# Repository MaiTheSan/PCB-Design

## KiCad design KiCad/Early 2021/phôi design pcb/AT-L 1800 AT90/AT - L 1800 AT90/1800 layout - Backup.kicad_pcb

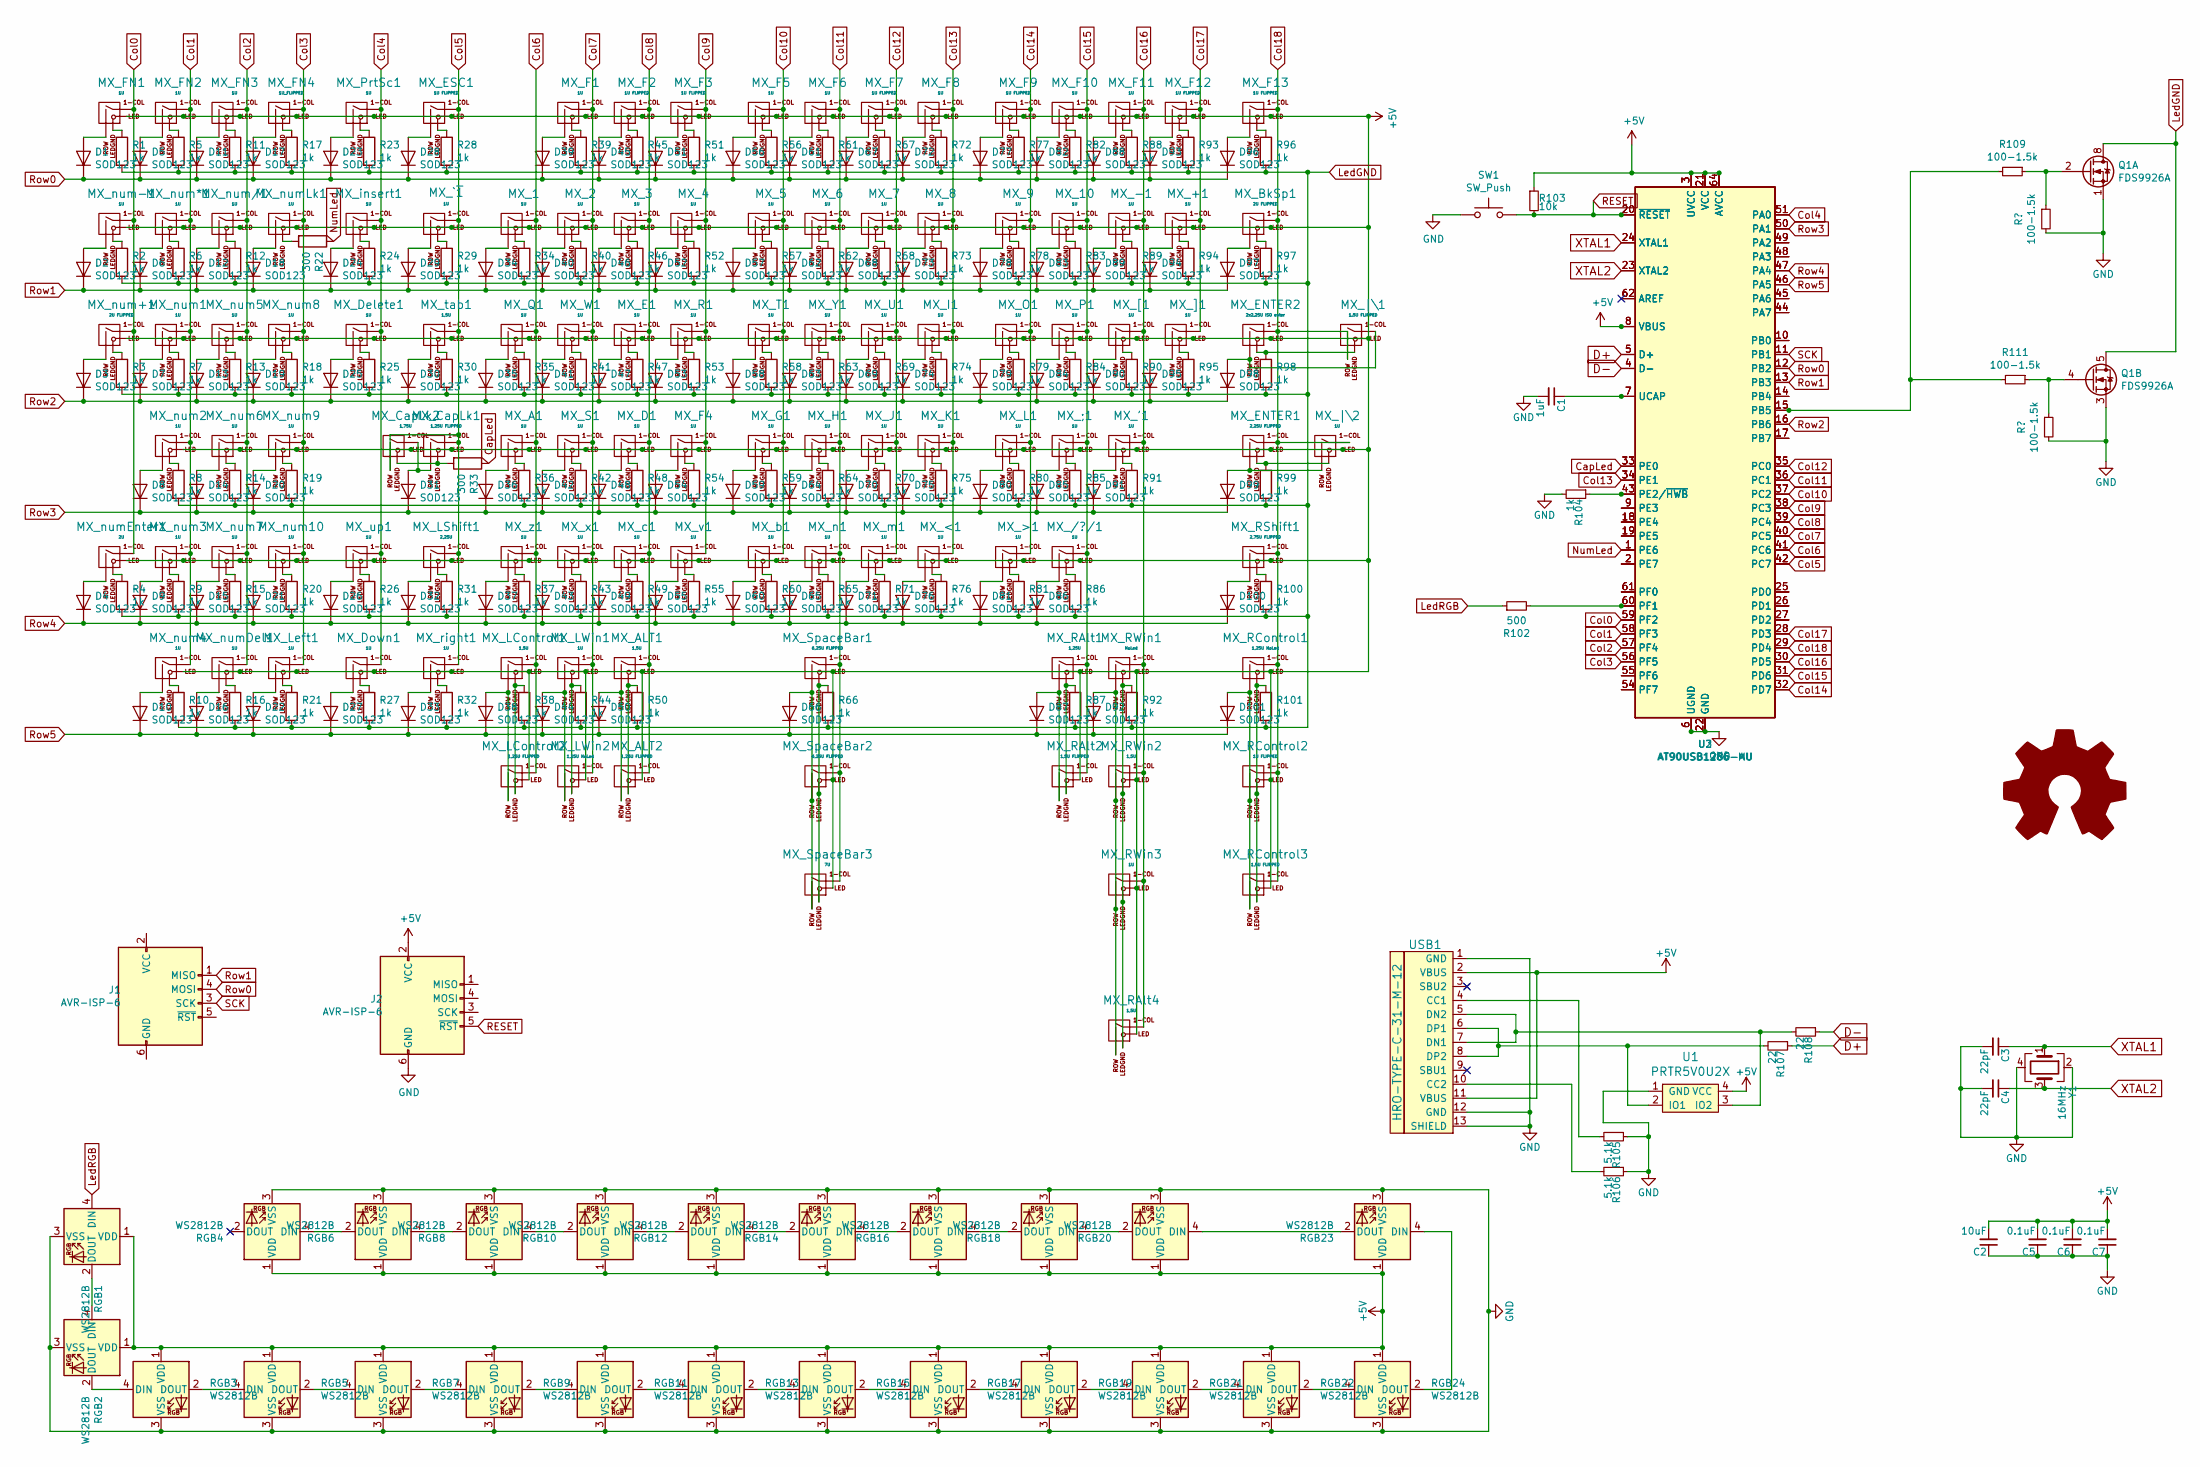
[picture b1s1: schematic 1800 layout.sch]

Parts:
C1: 1uF; C_0603
C2: 10uF; C_0603
C3, C4: 22pF; C_0603
C5, C6, C7: 0.1uF; C_0603
D1, D2, D3, D4, D5, D6, D7, D8, D9, D10, D11, D12, D13, D14, D15, D16, D17, D18, D19, D20, D21, D22, D23, D24, D25, D26, D27, D28, D29, D30, D31, D32, D33, D34, D35, D36, D37, D38, D39, D40, D41, D42, D43, D44, D45, D46, D47, D48, D49, D50, D51, D52, D53, D54, D55, D56, D57, D58, D59, D60, D61, D62, D63, D64, D65, D66, D67, D68, D69, D70, D71, D72, D73, D74, D75, D76, D77, D78, D79, D80, D81, D82, D83, D84, D85, D86, D87, D88, D89, D90, D91, D92, D93, D94, D95, D96, D97, D98, D99, D101: SOD123; D_SOD-123
D100: SOD123; D_SOD-123-Pretty
J1, J2: AVR-ISP-6; Reset_Pretty
LOGO1: Logo_Open_Hardware_Large; sanpjxlogo
MX_1, MX_2, MX_3, MX_4, MX_5, MX_6, MX_7, MX_8, MX_9, MX_10: 1U; MXOnly-1U
MX_'1: 1U; MXOnly-1U
MX_+1: 1U; MXOnly-1U
MX_-1: 1U; MXOnly-1U
MX_/?/1: 1U; MXOnly-1U
MX_;1: 1U; MXOnly-1U
MX_<1: 1U; MXOnly-1U
MX_>1: 1U; MXOnly-1U
MX_A1: 1U; MXOnly-1U
MX_ALT1: 1,5U; MXOnly-1.5U
MX_ALT2: 1,25U FLIPPED; MXOnly-1.25U-FLIPPED
MX_BkSp1: 2U FLIPPED; MXOnly-2U-FLIPPED
MX_CapLk1: 1,25U FLIPPED; MXOnly-1.25U-FLIPPED
MX_CapLk2: 1,75U; MXOnly-1.75U
MX_D1: 1U; MXOnly-1U
MX_Delete1: 1U; MXOnly-1U
MX_Down1: 1U; MXOnly-1U-FLIPPED
MX_E1: 1U; MXOnly-1U
MX_ENTER1: 2,25U FLIPPED; MXOnly-2.25U-FLIPPED-ReversedStabilizers
MX_ENTER2: 2x2.25U ISO enter; MXOnly-ISO
MX_ESC1: 1U FLIPPED; MXOnly-1U-FLIPPED
MX_F1, MX_F4, MX_F6, MX_F8, MX_F10, MX_F11: 1U; MXOnly-1U
MX_F2, MX_F3, MX_F7, MX_F9, MX_F12, MX_F13: 1U FLIPPED; MXOnly-1U-FLIPPED
MX_F5: 1U; MXOnly-1U-FLIPPED
MX_FN1, MX_FN2, MX_FN3: 1U; MXOnly-1U
MX_FN4: 1U_FLIPPED; MXOnly-1U-FLIPPED
MX_G1: 1U; MXOnly-1U
MX_H1: 1U; MXOnly-1U
MX_I1: 1U; MXOnly-1U
MX_J1: 1U; MXOnly-1U
MX_K1: 1U; MXOnly-1U
MX_L1: 1U; MXOnly-1U
MX_LControl1: 1,5U; MXOnly-1.5U
MX_LControl2: 1,25U FLIPPED; MXOnly-1.25U-FLIPPED
MX_LShift1: 2,25U; MXOnly-2.25U
MX_LWin1: 1U; MXOnly-1U
MX_LWin2: 1,25U NoLed; MXOnly-1.25U-FLIPPED
MX_Left1: 1U; MXOnly-1U
MX_O1: 1U; MXOnly-1U
MX_P1: 1U; MXOnly-1U
MX_PrtSc1: 1U; MXOnly-1U
MX_Q1: 1U; MXOnly-1U
MX_R1: 1U; MXOnly-1U
MX_RAlt1: 1,25U; MXOnly-1.25U
MX_RAlt2: 1,5U FLIPPED; MXOnly-1.5U-FLIPPED
MX_RAlt4: 1,5U; MXOnly-1.5U
MX_RControl1: 1,25U NoLed; MXOnly-1.25U
MX_RControl2: 1U FLIPPED; MXOnly-1U-FLIPPED
MX_RControl3: 1,5U FLIPPED; MXOnly-1.5U-FLIPPED
MX_RShift1: 2,75U FLIPPED; MXOnly-2.75U-FLIPPED
MX_RWin1: NoLed; MXOnly-1.25U-FLIPPED
MX_RWin2: 1,5U; MXOnly-1.5U
MX_RWin3: 1U; MXOnly-1U
MX_S1: 1U; MXOnly-1U
MX_SpaceBar1, MX_SpaceBar2: 6,25U FLIPPED; MXOnly-6.25U-FLIPPED-ReversedStabilizers
MX_SpaceBar3: 7U; MXOnly-7U-ReversedStabilizers
MX_T1: 1U; MXOnly-1U
MX_U1: 1U; MXOnly-1U
MX_W1: 1U; MXOnly-1U
MX_Y1: 1U; MXOnly-1U
MX_[1: 1U; MXOnly-1U
MX_]1: 1U; MXOnly-1U
MX_`~1: 1U; MXOnly-1U
MX_b1: 1U; MXOnly-1U
MX_c1: 1U; MXOnly-1U
MX_insert1: 1U; MXOnly-1U
MX_m1: 1U; MXOnly-1U
MX_n1: 1U; MXOnly-1U
MX_num1, MX_num2, MX_num3, MX_num4, MX_num5, MX_num6, MX_num7, MX_num9, MX_num10: 1U; MXOnly-1U
MX_num8: 1U; MXOnly-1U-FLIPPED
MX_num*1: 1U; MXOnly-1U
MX_num+1: 2U FLIPPED; MXOnly-2U
MX_num-1: 1U; MXOnly-1U
MX_num/1: 1U; MXOnly-1U
MX_numDel1: 1U; MXOnly-1U
MX_numEnter1: 2U; MXOnly-2U
MX_numLk1: 1U; MXOnly-1U
MX_right1: 1U; MXOnly-1U
MX_tab1: 1,5U; MXOnly-1.5U
MX_up1: 1U; MXOnly-1U
MX_v1: 1U; MXOnly-1U
MX_x1: 1U; MXOnly-1U
MX_z1: 1U; MXOnly-1U
MX_|\1: 1.5U FLIPPED; MXOnly-1.5U-FLIPPED
MX_|\2: 1U; MXOnly-1U
Q1: FDS9926A; SOIC-8_3.9x4.9mm_P1.27mm
R1, R2, R3, R4, R5, R6, R7, R8, R9, R10, R11, R12, R13, R14, R15, R16, R17, R18, R19, R20, R21, R23, R24, R25, R26, R27, R28, R29, R30, R31, R32, R34, R35, R36, R37, R38, R39, R40, R41, R42, R43, R44, R45, R46, R47, R48, R49, R50, R51, R52, R53, R54, R55, R56, R57, R58, R59, R60, R61, R62, R63, R64, R65, R66, R67, R68, R69, R70, R71, R72, R73, R74, R75, R76, R77, R78, R79, R80, R81, R82, R83, R84, R85, R86, R87, R88, R89, R90, R91, R92, R93, R94, R95, R96, R97, R98, R99, R100, R101, R104: 1k; R_0805
R22, R33: 300; R_0805
R102: 500; R_0805
R103: 10k; R_0805
R105, R106: 5.1k; C_0603
R107, R108: 22; C_0603
R109, R111: 100-1.5k; R_0805
RGB1, RGB2, RGB3, RGB4, RGB5, RGB6, RGB7, RGB8, RGB9, RGB10, RGB11, RGB12, RGB13, RGB14, RGB15, RGB16, RGB17, RGB18, RGB19, RGB20, RGB21, RGB22, RGB23, RGB24: WS2812B; LED_WS2812B_PLCC4_5.0x5.0mm_P3.2mm
SW1: SW_Push; SKQG-1155865
U1: PRTR5V0U2X; SOT143B
U2: AT90USB1286-AU; TQFP-64_14x14mm_P0.8mm
U3: AT90USB1286-MU; QFN-64-1EP_9x9mm_P0.5mm_EP7.5x7.5mm
USB1: HRO-TYPE-C-31-M-12; HRO-TYPE-C-31-M-12-Assembly
Y1: 16MHz; Crystal_SMD_3225-4Pin_3.2x2.5mm

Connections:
+5V: C2.2, C5.2, C6.2, C7.2, J2.2 (VCC), MX_1.3 (LED), MX_2.3 (LED), MX_3.3 (LED), MX_4.3 (LED), MX_5.3 (LED), MX_6.3 (LED), MX_7.3 (LED), MX_8.3 (LED), MX_9.3 (LED), MX_10.3 (LED), MX_'1.3 (LED), MX_+1.3 (LED), MX_-1.3 (LED), MX_/?/1.3 (LED), MX_;1.3 (LED), MX_<1.3 (LED), MX_>1.3 (LED), MX_A1.3 (LED), MX_ALT1.3 (LED), MX_ALT2.3 (LED), MX_BkSp1.3 (LED), MX_CapLk1.3 (LED), MX_CapLk2.3 (LED), MX_D1.3 (LED), MX_Delete1.3 (LED), MX_Down1.3 (LED), MX_E1.3 (LED), MX_ENTER1.3 (LED), MX_ENTER2.3 (LED), MX_ESC1.3 (LED), MX_F1.3 (LED), MX_F2.3 (LED), MX_F3.3 (LED), MX_F4.3 (LED), MX_F5.3 (LED), MX_F6.3 (LED), MX_F7.3 (LED), MX_F8.3 (LED), MX_F9.3 (LED), MX_F10.3 (LED), MX_F11.3 (LED), MX_F12.3 (LED), MX_F13.3 (LED), MX_FN1.3 (LED), MX_FN2.3 (LED), MX_FN3.3 (LED), MX_FN4.3 (LED), MX_G1.3 (LED), MX_H1.3 (LED), MX_I1.3 (LED), MX_J1.3 (LED), MX_K1.3 (LED), MX_L1.3 (LED), MX_LControl1.3 (LED), MX_LControl2.3 (LED), MX_LShift1.3 (LED), MX_LWin1.3 (LED), MX_LWin2.3 (LED), MX_Left1.3 (LED), MX_O1.3 (LED), MX_P1.3 (LED), MX_PrtSc1.3 (LED), MX_Q1.3 (LED), MX_R1.3 (LED), MX_RAlt1.3 (LED), MX_RAlt2.3 (LED), MX_RAlt4.3 (LED), MX_RControl1.3 (LED), MX_RControl2.3 (LED), MX_RControl3.3 (LED), MX_RShift1.3 (LED), MX_RWin1.3 (LED), MX_RWin2.3 (LED), MX_RWin3.3 (LED), MX_S1.3 (LED), MX_SpaceBar1.3 (LED), MX_SpaceBar2.3 (LED), MX_SpaceBar3.3 (LED), MX_T1.3 (LED), MX_U1.3 (LED), MX_W1.3 (LED), MX_Y1.3 (LED), MX_[1.3 (LED), MX_]1.3 (LED), MX_`~1.3 (LED), MX_b1.3 (LED), MX_c1.3 (LED), MX_insert1.3 (LED), MX_m1.3 (LED), MX_n1.3 (LED), MX_num1.3 (LED), MX_num2.3 (LED), MX_num3.3 (LED), MX_num4.3 (LED), MX_num5.3 (LED), MX_num6.3 (LED), MX_num7.3 (LED), MX_num8.3 (LED), MX_num9.3 (LED), MX_num10.3 (LED), MX_num*1.3 (LED), MX_num+1.3 (LED), MX_num-1.3 (LED), MX_num/1.3 (LED), MX_numDel1.3 (LED), MX_numEnter1.3 (LED), MX_numLk1.3 (LED), MX_right1.3 (LED), MX_tab1.3 (LED), MX_up1.3 (LED), MX_v1.3 (LED), MX_x1.3 (LED), MX_z1.3 (LED), MX_|\1.3 (LED), MX_|\2.3 (LED), R103.1, RGB1.1 (VDD), RGB2.1 (VDD), RGB3.1 (VDD), RGB4.1 (VDD), RGB5.1 (VDD), RGB6.1 (VDD), RGB7.1 (VDD), RGB8.1 (VDD), RGB9.1 (VDD), RGB10.1 (VDD), RGB11.1 (VDD), RGB12.1 (VDD), RGB13.1 (VDD), RGB14.1 (VDD), RGB15.1 (VDD), RGB16.1 (VDD), RGB17.1 (VDD), RGB18.1 (VDD), RGB19.1 (VDD), RGB20.1 (VDD), RGB21.1 (VDD), RGB22.1 (VDD), RGB23.1 (VDD), RGB24.1 (VDD), U1.4 (VCC), U2.3 (UVCC), U2.8 (VBUS), U2.21 (VCC), U2.52 (VCC), U2.64 (AVCC), U3.3 (UVCC), U3.8 (VBUS), U3.21 (VCC), U3.52 (VCC), U3.64 (AVCC), USB1.2 (VBUS), USB1.11 (VBUS)
CapLed: R33.1, U2.33 (PE0), U3.33 (PE0)
Col0: MX_FN1.1 (COL), MX_num+1.1 (COL), MX_num-1.1 (COL), MX_numEnter1.1 (COL), U2.59 (PF2), U3.59 (PF2)
Col1: MX_FN2.1 (COL), MX_num1.1 (COL), MX_num2.1 (COL), MX_num3.1 (COL), MX_num4.1 (COL), MX_num*1.1 (COL), U2.58 (PF3), U3.58 (PF3)
Col2: MX_FN3.1 (COL), MX_num5.1 (COL), MX_num6.1 (COL), MX_num7.1 (COL), MX_num/1.1 (COL), MX_numDel1.1 (COL), U2.57 (PF4), U3.57 (PF4)
Col3: MX_FN4.1 (COL), MX_Left1.1 (COL), MX_num8.1 (COL), MX_num9.1 (COL), MX_num10.1 (COL), MX_numLk1.1 (COL), U2.56 (PF5), U3.56 (PF5)
Col4: MX_Delete1.1 (COL), MX_Down1.1 (COL), MX_PrtSc1.1 (COL), MX_insert1.1 (COL), MX_up1.1 (COL), U2.51 (PA0), U3.51 (PA0)
Col5: MX_CapLk1.1 (COL), MX_CapLk2.2 (ROW), MX_ESC1.1 (COL), MX_LShift1.1 (COL), MX_`~1.1 (COL), MX_right1.1 (COL), MX_tab1.1 (COL), U2.42 (PC7), U3.42 (PC7)
Col6: MX_1.1 (COL), MX_A1.1 (COL), MX_LControl1.1 (COL), MX_LControl2.1 (COL), MX_Q1.1 (COL), MX_z1.1 (COL), U2.41 (PC6), U3.41 (PC6)
Col7: MX_2.1 (COL), MX_F1.1 (COL), MX_LWin1.1 (COL), MX_LWin2.1 (COL), MX_S1.1 (COL), MX_W1.1 (COL), MX_x1.1 (COL), U2.40 (PC5), U3.40 (PC5)
Col8: MX_3.1 (COL), MX_ALT1.1 (COL), MX_ALT2.1 (COL), MX_D1.1 (COL), MX_E1.1 (COL), MX_F2.1 (COL), MX_c1.1 (COL), U2.39 (PC4), U3.39 (PC4)
Col9: MX_4.1 (COL), MX_F3.1 (COL), MX_F4.1 (COL), MX_R1.1 (COL), MX_v1.1 (COL), U2.38 (PC3), U3.38 (PC3)
Col10: MX_5.1 (COL), MX_F5.1 (COL), MX_G1.1 (COL), MX_T1.1 (COL), MX_b1.1 (COL), U2.37 (PC2), U3.37 (PC2)
Col11: MX_6.1 (COL), MX_F6.1 (COL), MX_H1.1 (COL), MX_SpaceBar1.1 (COL), MX_SpaceBar2.1 (COL), MX_SpaceBar3.1 (COL), MX_Y1.1 (COL), MX_n1.1 (COL), U2.36 (PC1), U3.36 (PC1)
Col12: MX_7.1 (COL), MX_F7.1 (COL), MX_J1.1 (COL), MX_U1.1 (COL), MX_m1.1 (COL), U2.35 (PC0), U3.35 (PC0)
Col13: MX_8.1 (COL), MX_<1.1 (COL), MX_F8.1 (COL), MX_I1.1 (COL), MX_K1.1 (COL), U2.34 (PE1), U3.34 (PE1)
Col14: MX_9.1 (COL), MX_>1.1 (COL), MX_F9.1 (COL), MX_L1.1 (COL), MX_O1.1 (COL), U2.32 (PD7), U3.32 (PD7)
Col15: MX_10.1 (COL), MX_/?/1.1 (COL), MX_;1.1 (COL), MX_F10.1 (COL), MX_P1.1 (COL), MX_RAlt1.1 (COL), MX_RAlt2.1 (COL), U2.31 (PD6), U3.31 (PD6)
Col16: MX_'1.1 (COL), MX_-1.1 (COL), MX_F11.1 (COL), MX_RAlt4.1 (COL), MX_RWin1.1 (COL), MX_RWin2.1 (COL), MX_RWin3.1 (COL), MX_[1.1 (COL), U2.30 (PD5), U3.30 (PD5)
Col17: MX_+1.1 (COL), MX_F12.1 (COL), MX_]1.1 (COL), U2.28 (PD3), U3.28 (PD3)
Col18: MX_BkSp1.1 (COL), MX_ENTER1.1 (COL), MX_ENTER2.1 (COL), MX_F13.1 (COL), MX_RControl1.1 (COL), MX_RControl2.1 (COL), MX_RControl3.1 (COL), MX_RShift1.1 (COL), MX_|\1.2 (ROW), MX_|\2.1 (COL), U2.29 (PD4), U3.29 (PD4)
D+: R107.1, U2.5 (D+), U3.5 (D+)
D-: R108.1, U2.4 (D-), U3.4 (D-)
LedRGB: R102.1, RGB1.4 (DIN)
unnamed: C1.1, U2.7 (UCAP), U3.7 (UCAP)
unnamed: D1.2 (A), MX_FN1.2 (ROW)
unnamed: D2.2 (A), MX_num-1.2 (ROW)
unnamed: D3.2 (A), MX_num+1.2 (ROW)
unnamed: D4.2 (A), MX_numEnter1.2 (ROW)
unnamed: D5.2 (A), MX_FN2.2 (ROW)
unnamed: D6.2 (A), MX_num*1.2 (ROW)
unnamed: D7.2 (A), MX_num1.2 (ROW)
unnamed: D8.2 (A), MX_num2.2 (ROW)
unnamed: D9.2 (A), MX_num3.2 (ROW)
unnamed: D10.2 (A), MX_num4.2 (ROW)
unnamed: D11.2 (A), MX_FN3.2 (ROW)
unnamed: D12.2 (A), MX_num/1.2 (ROW)
unnamed: D13.2 (A), MX_num5.2 (ROW)
unnamed: D14.2 (A), MX_num6.2 (ROW)
unnamed: D15.2 (A), MX_num7.2 (ROW)
unnamed: D16.2 (A), MX_numDel1.2 (ROW)
unnamed: D17.2 (A), MX_FN4.2 (ROW)
unnamed: D18.2 (A), MX_numLk1.2 (ROW)
unnamed: D19.2 (A), MX_num8.2 (ROW)
unnamed: D20.2 (A), MX_num9.2 (ROW)
unnamed: D21.2 (A), MX_num10.2 (ROW)
unnamed: D22.2 (A), MX_Left1.2 (ROW)
unnamed: D23.2 (A), MX_PrtSc1.2 (ROW)
unnamed: D24.2 (A), MX_insert1.2 (ROW)
unnamed: D25.2 (A), MX_Delete1.2 (ROW)
unnamed: D26.2 (A), MX_up1.2 (ROW)
unnamed: D27.2 (A), MX_Down1.2 (ROW)
unnamed: D28.2 (A), MX_ESC1.2 (ROW)
unnamed: D29.2 (A), MX_`~1.2 (ROW)
unnamed: D30.2 (A), MX_tab1.2 (ROW)
unnamed: D31.2 (A), MX_CapLk1.2 (ROW), MX_CapLk2.1 (COL)
unnamed: D32.2 (A), MX_LShift1.2 (ROW)
unnamed: D33.2 (A), MX_right1.2 (ROW)
unnamed: D34.2 (A), MX_1.2 (ROW)
unnamed: D35.2 (A), MX_Q1.2 (ROW)
unnamed: D36.2 (A), MX_A1.2 (ROW)
unnamed: D37.2 (A), MX_z1.2 (ROW)
unnamed: D38.2 (A), MX_LControl1.2 (ROW), MX_LControl2.2 (ROW)
unnamed: D39.2 (A), MX_F1.2 (ROW)
unnamed: D40.2 (A), MX_2.2 (ROW)
unnamed: D41.2 (A), MX_W1.2 (ROW)
unnamed: D42.2 (A), MX_S1.2 (ROW)
unnamed: D43.2 (A), MX_x1.2 (ROW)
unnamed: D44.2 (A), MX_LWin1.2 (ROW), MX_LWin2.2 (ROW)
unnamed: D45.2 (A), MX_F2.2 (ROW)
unnamed: D46.2 (A), MX_3.2 (ROW)
unnamed: D47.2 (A), MX_E1.2 (ROW)
unnamed: D48.2 (A), MX_D1.2 (ROW)
unnamed: D49.2 (A), MX_c1.2 (ROW)
unnamed: D50.2 (A), MX_ALT1.2 (ROW), MX_ALT2.2 (ROW)
unnamed: D51.2 (A), MX_F3.2 (ROW)
unnamed: D52.2 (A), MX_4.2 (ROW)
unnamed: D53.2 (A), MX_R1.2 (ROW)
unnamed: D54.2 (A), MX_F4.2 (ROW)
unnamed: D55.2 (A), MX_v1.2 (ROW)
unnamed: D56.2 (A), MX_F5.2 (ROW)
unnamed: D57.2 (A), MX_5.2 (ROW)
unnamed: D58.2 (A), MX_T1.2 (ROW)
unnamed: D59.2 (A), MX_G1.2 (ROW)
unnamed: D60.2 (A), MX_b1.2 (ROW)
unnamed: D61.2 (A), MX_F6.2 (ROW)
unnamed: D62.2 (A), MX_6.2 (ROW)
unnamed: D63.2 (A), MX_Y1.2 (ROW)
unnamed: D64.2 (A), MX_H1.2 (ROW)
unnamed: D65.2 (A), MX_n1.2 (ROW)
unnamed: D66.2 (A), MX_SpaceBar1.2 (ROW), MX_SpaceBar2.2 (ROW), MX_SpaceBar3.2 (ROW)
unnamed: D67.2 (A), MX_F7.2 (ROW)
unnamed: D68.2 (A), MX_7.2 (ROW)
unnamed: D69.2 (A), MX_U1.2 (ROW)
unnamed: D70.2 (A), MX_J1.2 (ROW)
unnamed: D71.2 (A), MX_m1.2 (ROW)
unnamed: D72.2 (A), MX_F8.2 (ROW)
unnamed: D73.2 (A), MX_8.2 (ROW)
unnamed: D74.2 (A), MX_I1.2 (ROW)
unnamed: D75.2 (A), MX_K1.2 (ROW)
unnamed: D76.2 (A), MX_<1.2 (ROW)
unnamed: D77.2 (A), MX_F9.2 (ROW)
unnamed: D78.2 (A), MX_9.2 (ROW)
unnamed: D79.2 (A), MX_O1.2 (ROW)
unnamed: D80.2 (A), MX_L1.2 (ROW)
unnamed: D81.2 (A), MX_>1.2 (ROW)
unnamed: D82.2 (A), MX_F10.2 (ROW)
unnamed: D83.2 (A), MX_10.2 (ROW)
unnamed: D84.2 (A), MX_P1.2 (ROW)
unnamed: D85.2 (A), MX_;1.2 (ROW)
unnamed: D86.2 (A), MX_/?/1.2 (ROW)
unnamed: D87.2 (A), MX_RAlt1.2 (ROW), MX_RAlt2.2 (ROW)
unnamed: D88.2 (A), MX_F11.2 (ROW)
unnamed: D89.2 (A), MX_-1.2 (ROW)
unnamed: D90.2 (A), MX_[1.2 (ROW)
unnamed: D91.2 (A), MX_'1.2 (ROW)
unnamed: D92.2 (A), MX_RAlt4.2 (ROW), MX_RWin1.2 (ROW), MX_RWin2.2 (ROW), MX_RWin3.2 (ROW)
unnamed: D93.2 (A), MX_F12.2 (ROW)
unnamed: D94.2 (A), MX_+1.2 (ROW)
unnamed: D95.2 (A), MX_]1.2 (ROW)
unnamed: D96.2 (A), MX_F13.2 (ROW)
unnamed: D97.2 (A), MX_BkSp1.2 (ROW)
unnamed: D98.2 (A), MX_ENTER2.2 (ROW), MX_|\1.1 (COL)
unnamed: D99.2 (A), MX_ENTER1.2 (ROW), MX_|\2.2 (ROW)
unnamed: D100.2 (A), MX_RShift1.2 (ROW)
unnamed: D101.2 (A), MX_RControl1.2 (ROW), MX_RControl2.2 (ROW), MX_RControl3.2 (ROW)
unnamed: MX_1.4 (LEDGND), R34.1
unnamed: MX_2.4 (LEDGND), R40.1
unnamed: MX_3.4 (LEDGND), R46.1
unnamed: MX_4.4 (LEDGND), R52.1
unnamed: MX_5.4 (LEDGND), R57.1
unnamed: MX_6.4 (LEDGND), R62.1
unnamed: MX_7.4 (LEDGND), R68.1
unnamed: MX_8.4 (LEDGND), R73.1
unnamed: MX_9.4 (LEDGND), R78.1
unnamed: MX_10.4 (LEDGND), R83.1
unnamed: MX_'1.4 (LEDGND), R91.1
unnamed: MX_+1.4 (LEDGND), R94.1
unnamed: MX_-1.4 (LEDGND), R89.1
unnamed: MX_/?/1.4 (LEDGND), R86.1
unnamed: MX_;1.4 (LEDGND), R85.1
unnamed: MX_<1.4 (LEDGND), R76.1
unnamed: MX_>1.4 (LEDGND), R81.1
unnamed: MX_A1.4 (LEDGND), R36.1
unnamed: MX_ALT1.4 (LEDGND), MX_ALT2.4 (LEDGND), R50.1
unnamed: MX_BkSp1.4 (LEDGND), R97.1
unnamed: MX_CapLk1.4 (LEDGND), MX_CapLk2.4 (LEDGND), R33.2
unnamed: MX_D1.4 (LEDGND), R48.1
unnamed: MX_Delete1.4 (LEDGND), R25.1
unnamed: MX_Down1.4 (LEDGND), R27.1
unnamed: MX_E1.4 (LEDGND), R47.1
unnamed: MX_ENTER1.4 (LEDGND), MX_|\2.4 (LEDGND), R99.1
unnamed: MX_ENTER2.4 (LEDGND), MX_|\1.4 (LEDGND), R98.1
unnamed: MX_ESC1.4 (LEDGND), R28.1
unnamed: MX_F1.4 (LEDGND), R39.1
unnamed: MX_F2.4 (LEDGND), R45.1
unnamed: MX_F3.4 (LEDGND), R51.1
unnamed: MX_F4.4 (LEDGND), R54.1
unnamed: MX_F5.4 (LEDGND), R56.1
unnamed: MX_F6.4 (LEDGND), R61.1
unnamed: MX_F7.4 (LEDGND), R67.1
unnamed: MX_F8.4 (LEDGND), R72.1
unnamed: MX_F9.4 (LEDGND), R77.1
unnamed: MX_F10.4 (LEDGND), R82.1
unnamed: MX_F11.4 (LEDGND), R88.1
unnamed: MX_F12.4 (LEDGND), R93.1
unnamed: MX_F13.4 (LEDGND), R96.1
unnamed: MX_FN1.4 (LEDGND), R1.1
unnamed: MX_FN2.4 (LEDGND), R5.1
unnamed: MX_FN3.4 (LEDGND), R11.1
unnamed: MX_FN4.4 (LEDGND), R17.1
unnamed: MX_G1.4 (LEDGND), R59.1
unnamed: MX_H1.4 (LEDGND), R64.1
unnamed: MX_I1.4 (LEDGND), R74.1
unnamed: MX_J1.4 (LEDGND), R70.1
unnamed: MX_K1.4 (LEDGND), R75.1
unnamed: MX_L1.4 (LEDGND), R80.1
unnamed: MX_LControl1.4 (LEDGND), MX_LControl2.4 (LEDGND), R38.1
unnamed: MX_LShift1.4 (LEDGND), R31.1
unnamed: MX_LWin1.4 (LEDGND), MX_LWin2.4 (LEDGND), R44.1
unnamed: MX_Left1.4 (LEDGND), R21.1
unnamed: MX_O1.4 (LEDGND), R79.1
unnamed: MX_P1.4 (LEDGND), R84.1
unnamed: MX_PrtSc1.4 (LEDGND), R23.1
unnamed: MX_Q1.4 (LEDGND), R35.1
unnamed: MX_R1.4 (LEDGND), R53.1
unnamed: MX_RAlt1.4 (LEDGND), MX_RAlt2.4 (LEDGND), R87.1
unnamed: MX_RAlt4.4 (LEDGND), MX_RWin1.4 (LEDGND), MX_RWin2.4 (LEDGND), MX_RWin3.4 (LEDGND), R92.1
unnamed: MX_RControl1.4 (LEDGND), MX_RControl2.4 (LEDGND), MX_RControl3.4 (LEDGND), R101.1
unnamed: MX_RShift1.4 (LEDGND), R100.1
unnamed: MX_S1.4 (LEDGND), R42.1
unnamed: MX_SpaceBar1.4 (LEDGND), MX_SpaceBar2.4 (LEDGND), MX_SpaceBar3.4 (LEDGND), R66.1
unnamed: MX_T1.4 (LEDGND), R58.1
unnamed: MX_U1.4 (LEDGND), R69.1
unnamed: MX_W1.4 (LEDGND), R41.1
unnamed: MX_Y1.4 (LEDGND), R63.1
unnamed: MX_[1.4 (LEDGND), R90.1
unnamed: MX_]1.4 (LEDGND), R95.1
unnamed: MX_`~1.4 (LEDGND), R29.1
unnamed: MX_b1.4 (LEDGND), R60.1
unnamed: MX_c1.4 (LEDGND), R49.1
unnamed: MX_insert1.4 (LEDGND), R24.1
unnamed: MX_m1.4 (LEDGND), R71.1
unnamed: MX_n1.4 (LEDGND), R65.1
unnamed: MX_num1.4 (LEDGND), R7.1
unnamed: MX_num2.4 (LEDGND), R8.1
unnamed: MX_num3.4 (LEDGND), R9.1
unnamed: MX_num4.4 (LEDGND), R10.1
unnamed: MX_num5.4 (LEDGND), R13.1
unnamed: MX_num6.4 (LEDGND), R14.1
unnamed: MX_num7.4 (LEDGND), R15.1
unnamed: MX_num8.4 (LEDGND), R18.1
unnamed: MX_num9.4 (LEDGND), R19.1
unnamed: MX_num10.4 (LEDGND), R20.1
unnamed: MX_num*1.4 (LEDGND), R6.1
unnamed: MX_num+1.4 (LEDGND), R3.1
unnamed: MX_num-1.4 (LEDGND), R2.1
unnamed: MX_num/1.4 (LEDGND), R12.1
unnamed: MX_numDel1.4 (LEDGND), R16.1
unnamed: MX_numEnter1.4 (LEDGND), R4.1
unnamed: MX_numLk1.4 (LEDGND), R22.2
unnamed: MX_right1.4 (LEDGND), R32.1
unnamed: MX_tab1.4 (LEDGND), R30.1
unnamed: MX_up1.4 (LEDGND), R26.1
unnamed: MX_v1.4 (LEDGND), R55.1
unnamed: MX_x1.4 (LEDGND), R43.1
unnamed: MX_z1.4 (LEDGND), R37.1
unnamed: R102.2, U2.60 (PF1), U3.60 (PF1)
unnamed: R104.1, U2.43 (PE2/~HWB), U3.43 (PE2/~HWB)
unnamed: R105.2, USB1.4 (CC1)
unnamed: R106.2, USB1.10 (CC2)
unnamed: R107.2, U1.2 (IO1), USB1.6 (DP1), USB1.8 (DP2)
unnamed: R108.2, U1.3 (IO2), USB1.5 (DN2), USB1.7 (DN1)
unnamed: R109.2, R111.2, U2.15 (PB5), U3.15 (PB5)
unnamed: Q1.4 (G2), R111.1
unnamed: RGB1.2 (DOUT), RGB2.4 (DIN)
unnamed: RGB2.2 (DOUT), RGB3.4 (DIN)
unnamed: RGB3.2 (DOUT), RGB5.4 (DIN)
unnamed: RGB4.4 (DIN), RGB6.2 (DOUT)
unnamed: RGB5.2 (DOUT), RGB7.4 (DIN)
unnamed: RGB6.4 (DIN), RGB8.2 (DOUT)
unnamed: RGB7.2 (DOUT), RGB9.4 (DIN)
unnamed: RGB8.4 (DIN), RGB10.2 (DOUT)
unnamed: RGB10.4 (DIN), RGB12.2 (DOUT)
unnamed: RGB11.2 (DOUT), RGB13.4 (DIN)
unnamed: RGB9.2 (DOUT), RGB11.4 (DIN)
unnamed: RGB12.4 (DIN), RGB14.2 (DOUT)
unnamed: RGB13.2 (DOUT), RGB15.4 (DIN)
unnamed: RGB14.4 (DIN), RGB16.2 (DOUT)
unnamed: RGB15.2 (DOUT), RGB17.4 (DIN)
unnamed: RGB16.4 (DIN), RGB18.2 (DOUT)
unnamed: RGB17.2 (DOUT), RGB19.4 (DIN)
unnamed: RGB18.4 (DIN), RGB20.2 (DOUT)
unnamed: RGB19.2 (DOUT), RGB21.4 (DIN)
unnamed: RGB20.4 (DIN), RGB23.2 (DOUT)
unnamed: RGB21.2 (DOUT), RGB22.4 (DIN)
unnamed: RGB22.2 (DOUT), RGB24.4 (DIN)
unnamed: RGB23.4 (DIN), RGB24.2 (DOUT)
unnamed: U2.2 (PE7), U3.2 (PE7)
unnamed: U2.9 (PE3), U3.9 (PE3)
unnamed: U2.10 (PB0), U3.10 (PB0)
unnamed: U2.14 (PB4), U3.14 (PB4)
unnamed: U2.17 (PB7), U3.17 (PB7)
unnamed: U2.18 (PE4), U3.18 (PE4)
unnamed: U2.19 (PE5), U3.19 (PE5)
unnamed: U2.25 (PD0), U3.25 (PD0)
unnamed: U2.26 (PD1), U3.26 (PD1)
unnamed: U2.27 (PD2), U3.27 (PD2)
unnamed: U2.44 (PA7), U3.44 (PA7)
unnamed: U2.45 (PA6), U3.45 (PA6)
unnamed: U2.48 (PA3), U3.48 (PA3)
unnamed: U2.49 (PA2), U3.49 (PA2)
unnamed: U2.54 (PF7), U3.54 (PF7)
unnamed: U2.55 (PF6), U3.55 (PF6)
unnamed: U2.61 (PF0), U3.61 (PF0)
unnamed: U2.62 (AREF), U3.62 (AREF)
NumLed: R22.1, U2.1 (PE6), U3.1 (PE6)
RESET: J2.5 (~RST), R103.2, SW1.2, U2.20 (~RESET), U3.20 (~RESET)
Row0: D1.1 (K), D5.1 (K), D11.1 (K), D17.1 (K), D23.1 (K), D28.1 (K), D39.1 (K), D45.1 (K), D51.1 (K), D56.1 (K), D61.1 (K), D67.1 (K), D72.1 (K), D77.1 (K), D82.1 (K), D88.1 (K), D93.1 (K), D96.1 (K), J1.4 (MOSI), U2.12 (PB2), U3.12 (PB2)
Row1: D2.1 (K), D6.1 (K), D12.1 (K), D18.1 (K), D24.1 (K), D29.1 (K), D34.1 (K), D40.1 (K), D46.1 (K), D52.1 (K), D57.1 (K), D62.1 (K), D68.1 (K), D73.1 (K), D78.1 (K), D83.1 (K), D89.1 (K), D94.1 (K), D97.1 (K), J1.1 (MISO), U2.13 (PB3), U3.13 (PB3)
Row2: D3.1 (K), D7.1 (K), D13.1 (K), D19.1 (K), D25.1 (K), D30.1 (K), D35.1 (K), D41.1 (K), D47.1 (K), D53.1 (K), D58.1 (K), D63.1 (K), D69.1 (K), D74.1 (K), D79.1 (K), D84.1 (K), D90.1 (K), D95.1 (K), D98.1 (K), U2.16 (PB6), U3.16 (PB6)
Row3: D8.1 (K), D14.1 (K), D20.1 (K), D31.1 (K), D36.1 (K), D42.1 (K), D48.1 (K), D54.1 (K), D59.1 (K), D64.1 (K), D70.1 (K), D75.1 (K), D80.1 (K), D85.1 (K), D91.1 (K), D99.1 (K), U2.50 (PA1), U3.50 (PA1)
Row4: D4.1 (K), D9.1 (K), D15.1 (K), D21.1 (K), D26.1 (K), D32.1 (K), D37.1 (K), D43.1 (K), D49.1 (K), D55.1 (K), D60.1 (K), D65.1 (K), D71.1 (K), D76.1 (K), D81.1 (K), D86.1 (K), D100.1 (K), U2.47 (PA4), U3.47 (PA4)
Row5: D10.1 (K), D16.1 (K), D22.1 (K), D27.1 (K), D33.1 (K), D38.1 (K), D44.1 (K), D50.1 (K), D66.1 (K), D87.1 (K), D92.1 (K), D101.1 (K), U2.46 (PA5), U3.46 (PA5)
SCK: J1.3 (SCK), U2.11 (PB1), U3.11 (PB1)
XTAL1: C3.1, U2.24 (XTAL1), U3.24 (XTAL1), Y1.1
XTAL2: C4.1, U2.23 (XTAL2), U3.23 (XTAL2), Y1.3

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
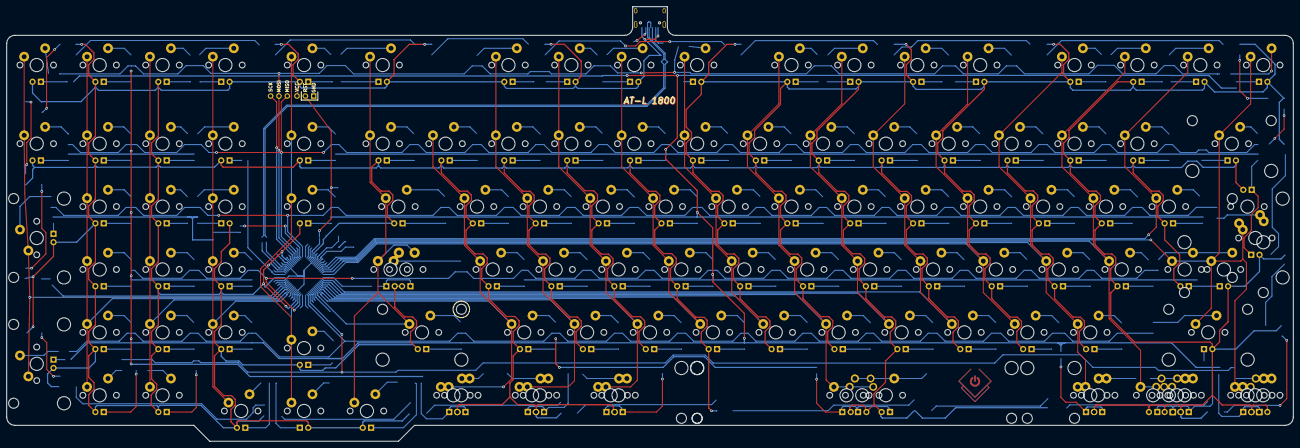
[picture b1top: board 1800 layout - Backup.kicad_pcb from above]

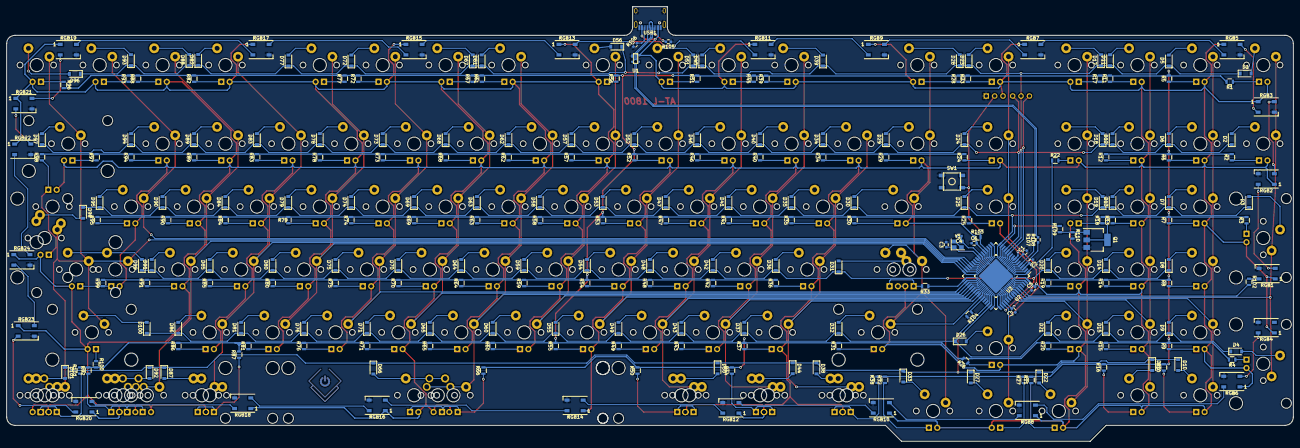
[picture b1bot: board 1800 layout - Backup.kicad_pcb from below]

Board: 2 copper layers, 389.7 x 131.6 mm, 367 parts (249 on the bottom side), 289 nets.

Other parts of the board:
R110: 10k; R_0805
